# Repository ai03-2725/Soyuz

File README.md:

# Soyuz
A single-PCB numpad kit

#### In light of recent claims that I am 100% liable for any of my open source PCBs, I am adding this disclaimer.
#### I provide these PCBs as a reference for designing keyboard PCBs. Using them within your projects will require a will to do research of one's own and to learn the workings of them, potentially fixing issues if they exist.
# I provide these PCBs without liability and without any guarantees regarding functionality, as expressed in the MIT license under which all of these PCBs are licensed.

### Build guides
[English](https://github.com/ai03-2725/Soyuz/blob/master/BuildGuide-English.md)
[日本語](https://github.com/ai03-2725/Soyuz/blob/master/BuildGuide-Japanese.md)

### Customizing guide for vendors
[English](https://github.com/ai03-2725/Soyuz/blob/master/VendorGuide-English.md)
[日本語](https://github.com/ai03-2725/Soyuz/blob/master/VendorGuide-Japanese.md)

### Purchasing
If you don't wish to go through the hassle of ordering direct from a fab using gerbers, the board is available for sale at the following:  
* [Spacecat Design](https://spacecat.design/collections/pcbs-cases-kits/products/soyuz-number-pad-kit)
* Yusha Kobo (Available for sale at the physical storefront)

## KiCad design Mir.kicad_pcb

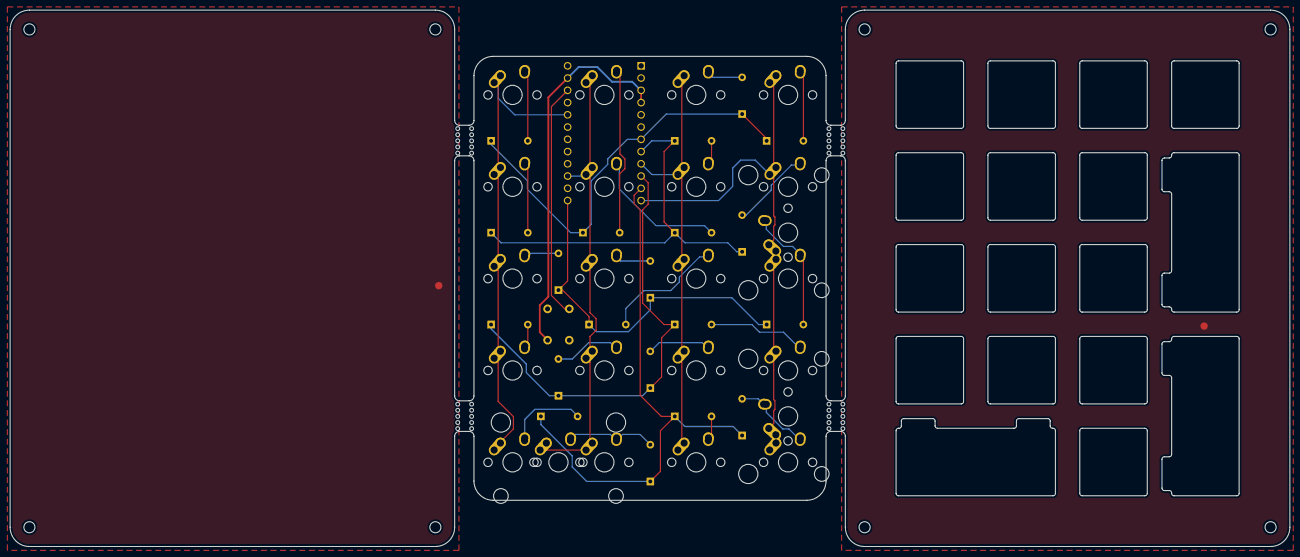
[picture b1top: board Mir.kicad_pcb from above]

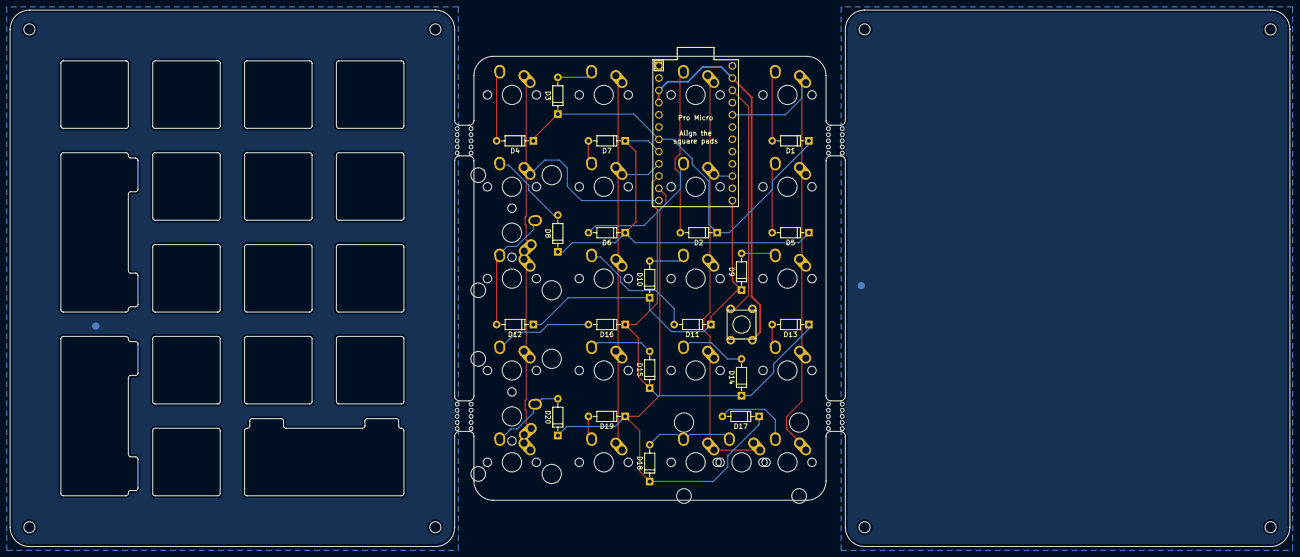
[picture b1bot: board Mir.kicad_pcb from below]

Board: 2 copper layers, 265.4 x 111.2 mm, 54 parts (22 on the bottom side), 31 nets.

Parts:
D1, D2, D3, D4, D5, D6, D7, D8, D9, D10, D11, D12, D13, D14, D15, D16, D17, D18, D19, D20: 1N4148; D_DO-35_SOD27_P7.62mm_Horizontal
MOUSEBITE1, MOUSEBITE2, MOUSEBITE3, MOUSEBITE4, MOUSEBITE5, MOUSEBITE6, MOUSEBITE7, MOUSEBITE8: Mousebites; breakaway-mousebites
MX1, MX2, MX3, MX4, MX5, MX6, MX7, MX8, MX10, MX11, MX12, MX13, MX14, MX15, MX16, MX17, MX19, MX20, MX21, MX22: MX-1U; MX-1U-NoLED
MX9, MX18, MX23: MX-2U; MX-2U-ReversedStabilizers-NoLED
O1: Outline; outline
SW1: SW_Push; PushButton_6x6mm_TH_Pretty
U1: ProMicro; ProMicro-EnforcedTop

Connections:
COL0: MX1.1, MX5.1, MX10.1, MX14.1, MX19.1, U1.20
COL1: MX2.1, MX6.1, MX11.1, MX15.1, MX20.1, MX23.1, U1.15
COL2: MX3.1, MX7.1, MX12.1, MX16.1, MX21.1, U1.9
COL3: MX4.1, MX8.1, MX9.1, MX13.1, MX17.1, MX18.1, MX22.1, U1.12
GND: SW1.2, U1.3, U1.4, U1.23
unnamed: D1.2, MX1.2
unnamed: D2.2, MX2.2
unnamed: D3.2, MX3.2
unnamed: D4.2, MX4.2
unnamed: D5.2, MX5.2
unnamed: D6.2, MX6.2
unnamed: D7.2, MX7.2
unnamed: D8.2, MX8.2
unnamed: D9.2, MX10.2
unnamed: D10.2, MX11.2
unnamed: D11.2, MX12.2
unnamed: D12.2, MX9.2, MX13.2
unnamed: D13.2, MX14.2
unnamed: D14.2, MX15.2
unnamed: D15.2, MX16.2
unnamed: D16.2, MX17.2
unnamed: D17.2, MX19.2
unnamed: D18.2, MX20.2, MX23.2
unnamed: D19.2, MX21.2
unnamed: D20.2, MX18.2, MX22.2
unnamed: SW1.1, U1.22
ROW0: D1.1, D2.1, D3.1, D4.1, U1.7
ROW1: D5.1, D6.1, D7.1, D8.1, U1.8
ROW2: D9.1, D10.1, D11.1, D12.1, U1.13
ROW3: D13.1, D14.1, D15.1, D16.1, U1.10
ROW4: D17.1, D18.1, D19.1, D20.1, U1.11

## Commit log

2019-01-13 Create empty project
2019-01-13 Add submodules
2019-01-14 Create outline, begin routing
2019-01-14 Routed
2019-01-14 Add ground fills
2019-01-14 Rename project
2019-01-14 Create production data
2019-01-14 Add image
2019-01-14 Build a readme template
2019-01-14 Write build guides
2019-01-14 Link build guides
2019-01-14 Write vendor customization guides
2019-01-14 Link vendor guide
2019-01-14 Update spacer dimens
2019-01-31 Update bottom plate artwork
2019-01-31 Repair silkscreen
2019-02-06 Add generic firmware files
2019-03-11 Add videos
2019-05-27 Update LICENSE
2019-06-08 Update build guides
2019-06-08 Remove the outdated firmware files
2019-06-08 Add vendors list
